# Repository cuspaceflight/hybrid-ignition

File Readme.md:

# Hybrid Rocket Engine Ignition System

This repository contains the design files for the valve controller used by CU Spaceflight to control our hybrid rocket engine. It is capable of actuating up to 10x 24W solenoid valves simultaneously and is controlled over RS422 or USB by a GUI. 

### Repository Layout

* **ChibiOS:** ChibiOS RTOS, developed by Giovanni Di Sirio.
* **agg-kicad:** KiCAD libraries, footprints and scripts developed by Adam Greig.
* **gen-board.h:** Python tool for generating 'board.h' header files for STM32 microcontrollers for use with ChibiOS.
* **m4-gcs:** Python GUI used to control and monitor the valve controller, developed by Greg Brooks.
* **pcb:** Hardware design files including schematic, pcb layout and BOM.
    * **comms:** Communications board project files.
    * **ignition:** Ignition board project files.
    * **lib:** Various schematic symbols.
* **firmware:** Firmware for each of the three sub-systems.
    * **comms-relay:** Full duplex USB to RS422 converter.
    * **comms-router:** Communications interface for the valve controller. Handles receiving packets over RS422 and routing to the firing boards over UART and vice-versa.
    * **ignition:** Actuates valves on command and reports measurements such as currents consumption, output voltage and if the valve coil is plugged in or not.

Developed by Matt Coates (mc955).

### Future Modifications
* The firing LEDs have their cathodes driven to 24v when a channel is armed but not firing. These LEDs should be moved to be driven by the GPIO that drives the gate of the firing FET.
* Flyback diodes are required on the output channels.

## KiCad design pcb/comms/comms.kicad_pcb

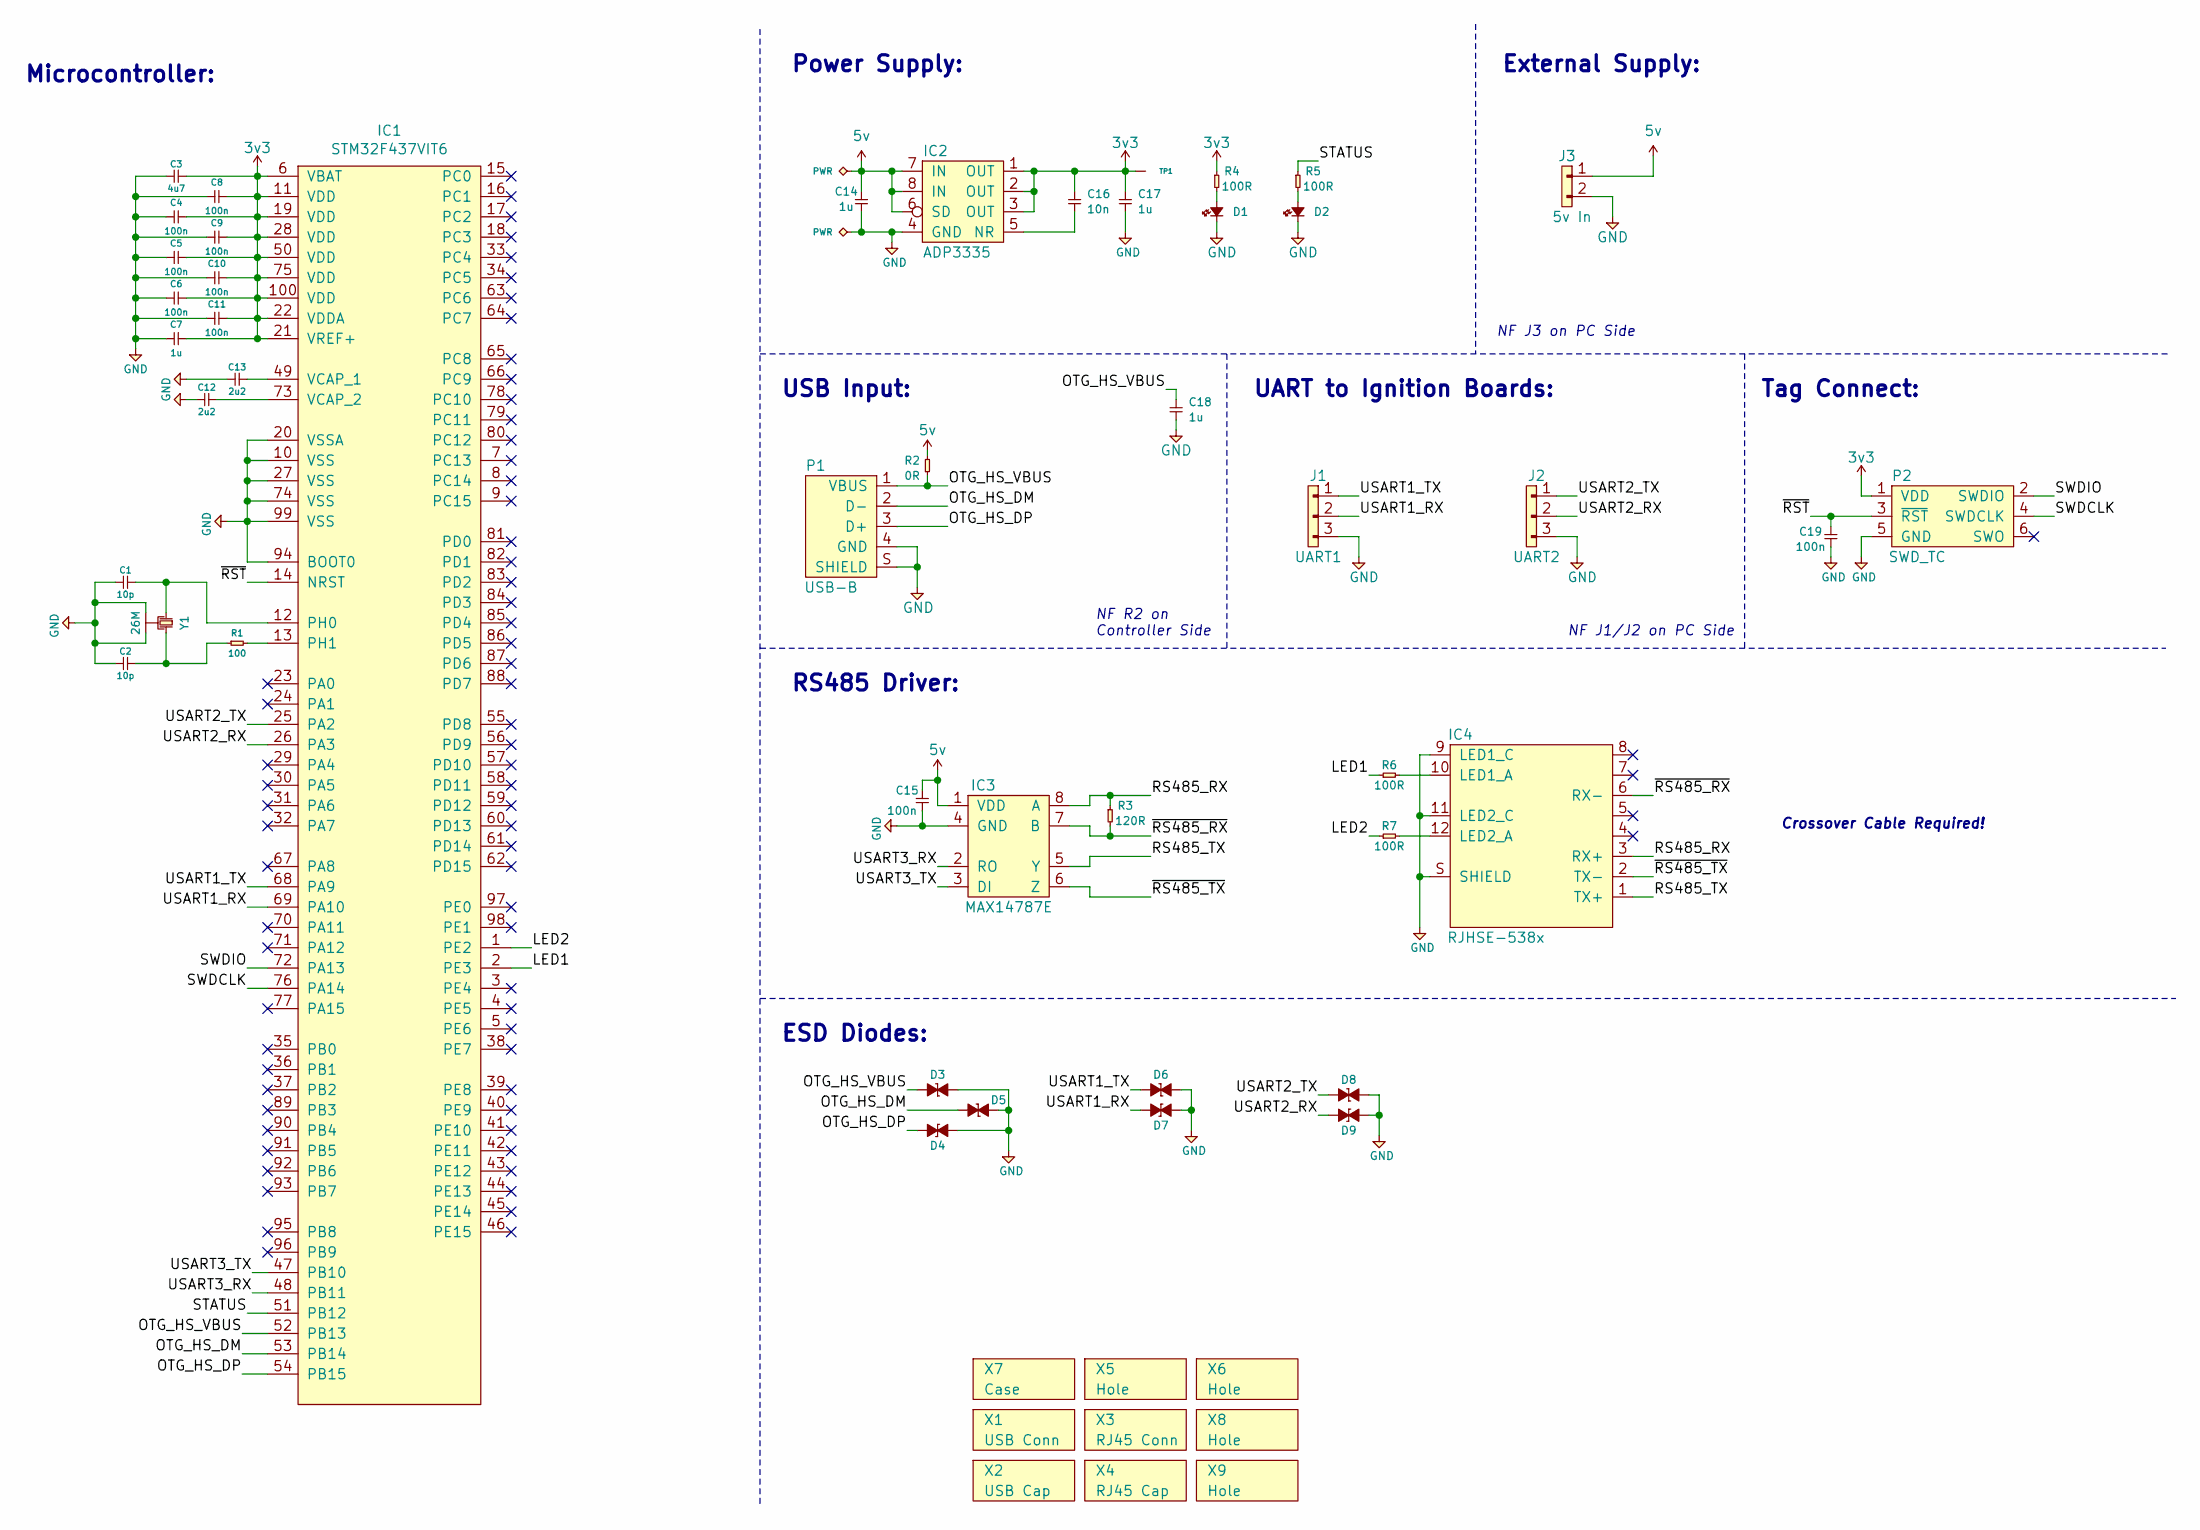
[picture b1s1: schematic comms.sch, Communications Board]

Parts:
C1, C2: 10p; 0402; Farnell 2496790
C3: 4u7; 0402; Farnell 2426952
C4, C5, C6, C8, C9, C10, C11, C15, C19: 100n; 0402; Farnell 2496771
C7: 1u; 0402; Farnell 2496814
C12, C13: 2u2; 0402; Farnell 2362088
C14, C17, C18: 1u; 0603-L; Farnell 1865556
C16: 10n; 0603-L; Farnell 2496825
D1, D2: LED; 0603-LED; Farnell 2290328
D3, D4, D5, D6, D7, D8, D9: ESD_DIODE; 0402; Farnell 2368169
IC1: STM32F437VIT6; LQFP-100; Farnell 2333377
IC2: ADP3335; MSOP-8; Farnell 2067775
IC3: MAX14787E; SOIC-8; Farnell 2528531
IC4: RJHSE-538x; RJHSE-538X; Farnell 1462758
J1: UART1; S03B-PASK-2; Farnell 1830748
J2: UART2; S03B-PASK-2; Farnell 1830748
J3: 5v In; S02B-PASK-2; Farnell 1830747
P1: USB-B; USB-B-SKT; Farnell 1753809
P2: SWD_TC; TC2030-NL
R1: 100; 0402; Farnell 9239111
R2: 0R; 0603; Farnell 2122112
R3: 120R; 0402; Farnell 2140682
R4, R5, R6, R7: 100R; 0603; Farnell 2616742
TP1: TESTPAD
X1: USB Conn
X2: USB Cap
X3: RJ45 Conn
X4: RJ45 Cap
X5, X6, X8, X9: Hole; M3_MOUNT
X7: Case; Farnell 9287787
Y1: 26M; XTAL-20x16; Farnell 2506952

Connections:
3v3: C3.2, C4.2, C5.2, C6.2, C7.2, C8.2, C9.2, C10.2, C11.2, C16.1, C17.1, IC1.6 (VBAT), IC1.11 (VDD), IC1.19 (VDD), IC1.21 (VREF+), IC1.22 (VDDA), IC1.28 (VDD), IC1.50 (VDD), IC1.75 (VDD), IC1.100 (VDD), IC2.1 (OUT), IC2.2 (OUT), IC2.3 (OUT), P2.1 (VDD), R4.1, TP1.1
5v: C14.1, C15.2, IC2.6 (SD), IC2.7 (IN), IC2.8 (IN), IC3.1 (VDD), J3.1, R2.2
/LED1: IC1.2 (PE3), R6.1
/LED2: IC1.1 (PE2), R7.1
/OTG_HS_DM: D5.1, IC1.53 (PB14), P1.2 (D-)
/OTG_HS_DP: D4.1, IC1.54 (PB15), P1.3 (D+)
/OTG_HS_VBUS: C18.1, D3.1, IC1.52 (PB13), P1.1 (VBUS), R2.1
/RS485_RX: IC3.8 (A), IC4.3 (RX+), R3.1
/RS485_TX: IC3.5 (Y), IC4.1 (TX+)
/STATUS: IC1.51 (PB12), R5.1
/SWDCLK: IC1.76 (PA14), P2.4 (SWDCLK)
/SWDIO: IC1.72 (PA13), P2.2 (SWDIO)
/USART1_RX: D7.1, IC1.69 (PA10), J1.2
/USART1_TX: D6.1, IC1.68 (PA9), J1.1
/USART2_RX: D9.1, IC1.26 (PA3), J2.2
/USART2_TX: D8.1, IC1.25 (PA2), J2.1
/USART3_RX: IC1.48 (PB11), IC3.2 (RO)
/USART3_TX: IC1.47 (PB10), IC3.3 (DI)
/~RS485_RX: IC3.7 (B), IC4.6 (RX-), R3.2
/~RS485_TX: IC3.6 (Z), IC4.2 (TX-)
/~RST: C19.2, IC1.14 (NRST), P2.3 (~RST)
GND: C1.1, C2.1, C3.1, C4.1, C5.1, C6.1, C7.1, C8.1, C9.1, C10.1, C11.1, C12.2, C13.2, C14.2, C15.1, C17.2, C18.2, C19.1, D1.1, D2.1, D3.2, D4.2, D5.2, D6.2, D7.2, D8.2, D9.2, IC1.10 (VSS), IC1.20 (VSSA), IC1.27 (VSS), IC1.74 (VSS), IC1.94 (BOOT0), IC1.99 (VSS), IC2.4 (GND), IC3.4 (GND), IC4.9 (LED1_C), IC4.11 (LED2_C), IC4.S (SHIELD), J1.3, J2.3, J3.2, P1.4 (GND), P1.S (SHIELD), P2.5 (GND), Y1.2, Y1.4
unnamed: C1.2, IC1.12 (PH0), Y1.1
unnamed: C2.2, R1.1, Y1.3
unnamed: C12.1, IC1.73 (VCAP_2)
unnamed: C13.1, IC1.49 (VCAP_1)
unnamed: C16.2, IC2.5 (NR)
unnamed: D1.2, R4.2
unnamed: D2.2, R5.2
unnamed: IC1.13 (PH1), R1.2
unnamed: IC4.10 (LED1_A), R6.2
unnamed: IC4.12 (LED2_A), R7.2

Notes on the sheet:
Microcontroller:
Power Supply:
Tag Connect:
USB Input:
External Supply:
RS485 Driver:
UART to Ignition Boards:
Crossover Cable Required!
NF J1/J2 on PC Side
NF J3 on PC Side
NF R2 on Controller Side
ESD Diodes:

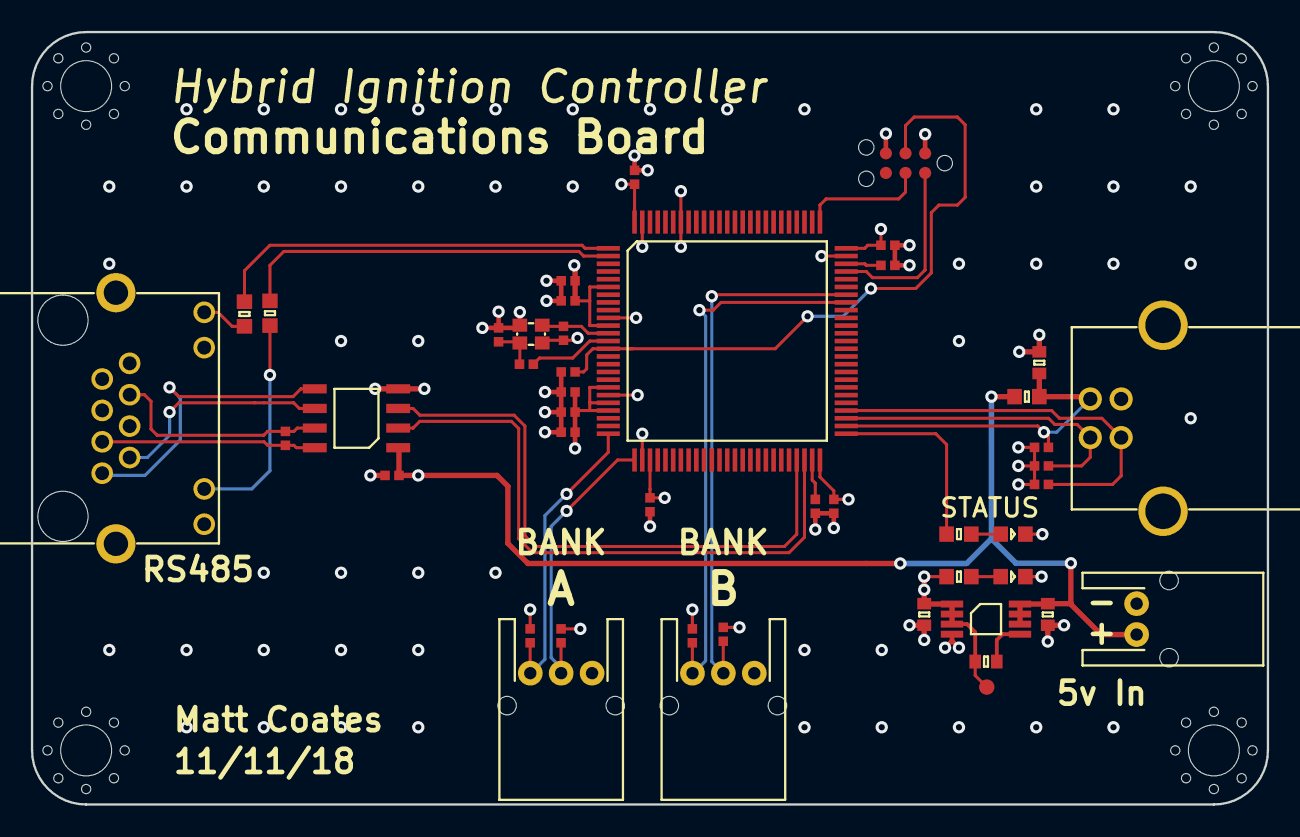
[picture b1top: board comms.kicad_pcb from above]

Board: 4 copper layers, 80.0 x 50.0 mm, 50 parts (0 on the bottom side), 32 nets.

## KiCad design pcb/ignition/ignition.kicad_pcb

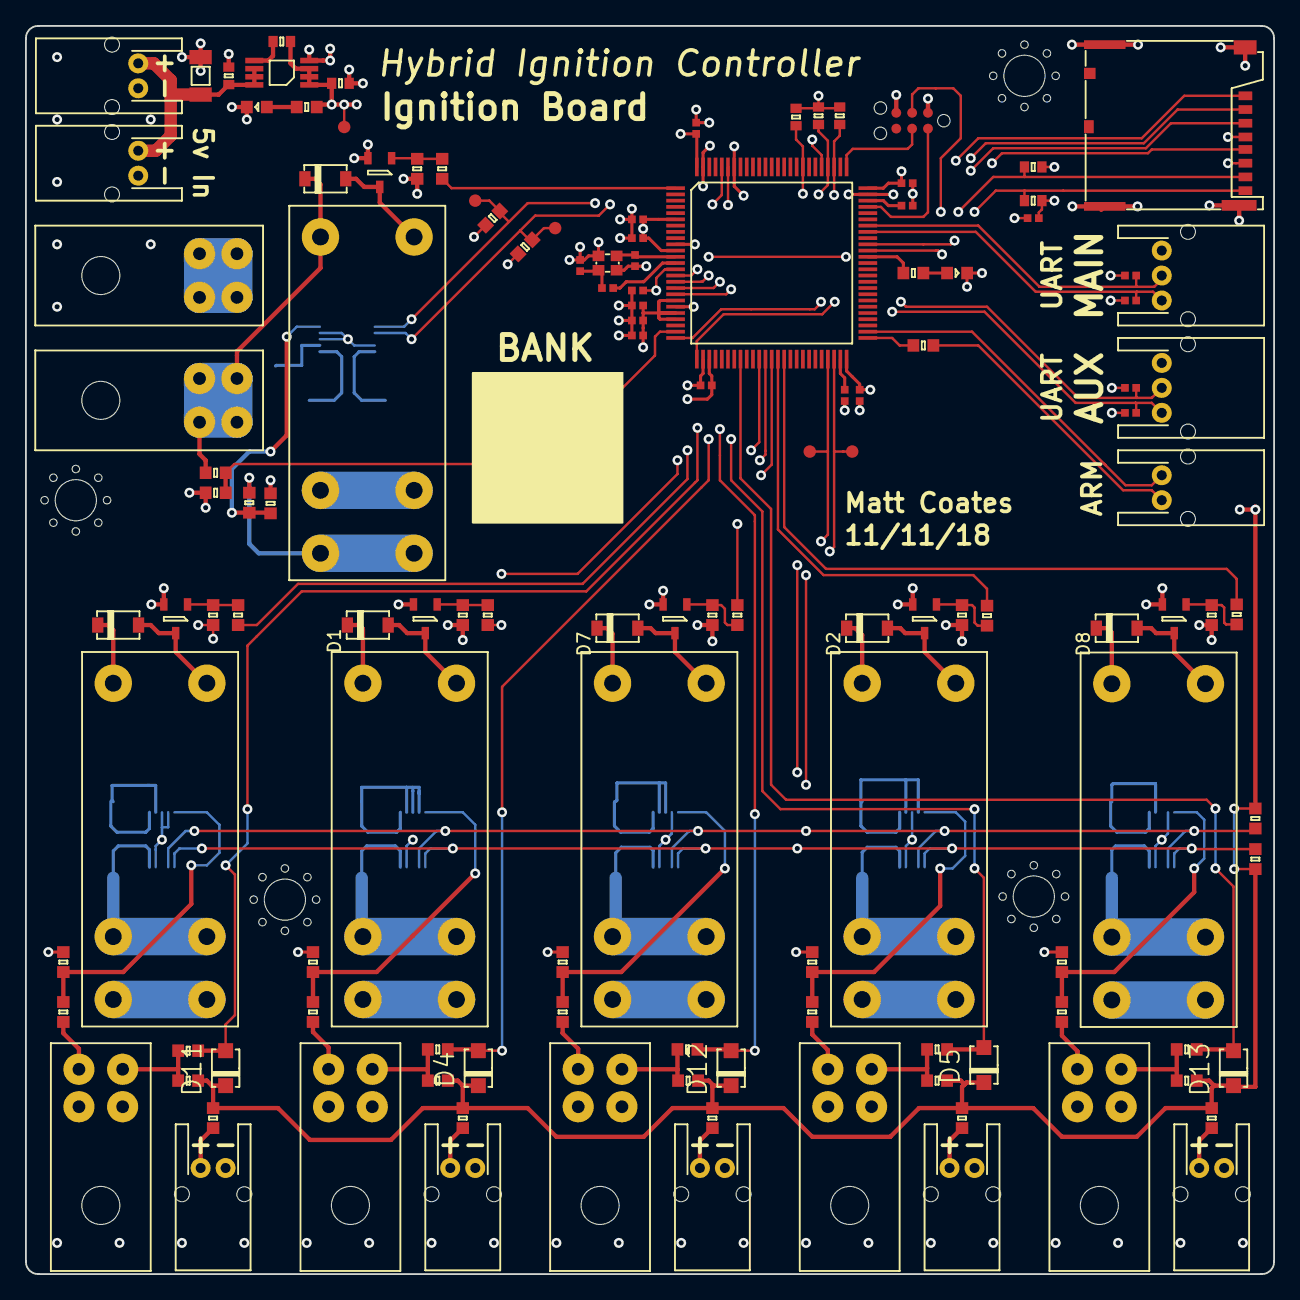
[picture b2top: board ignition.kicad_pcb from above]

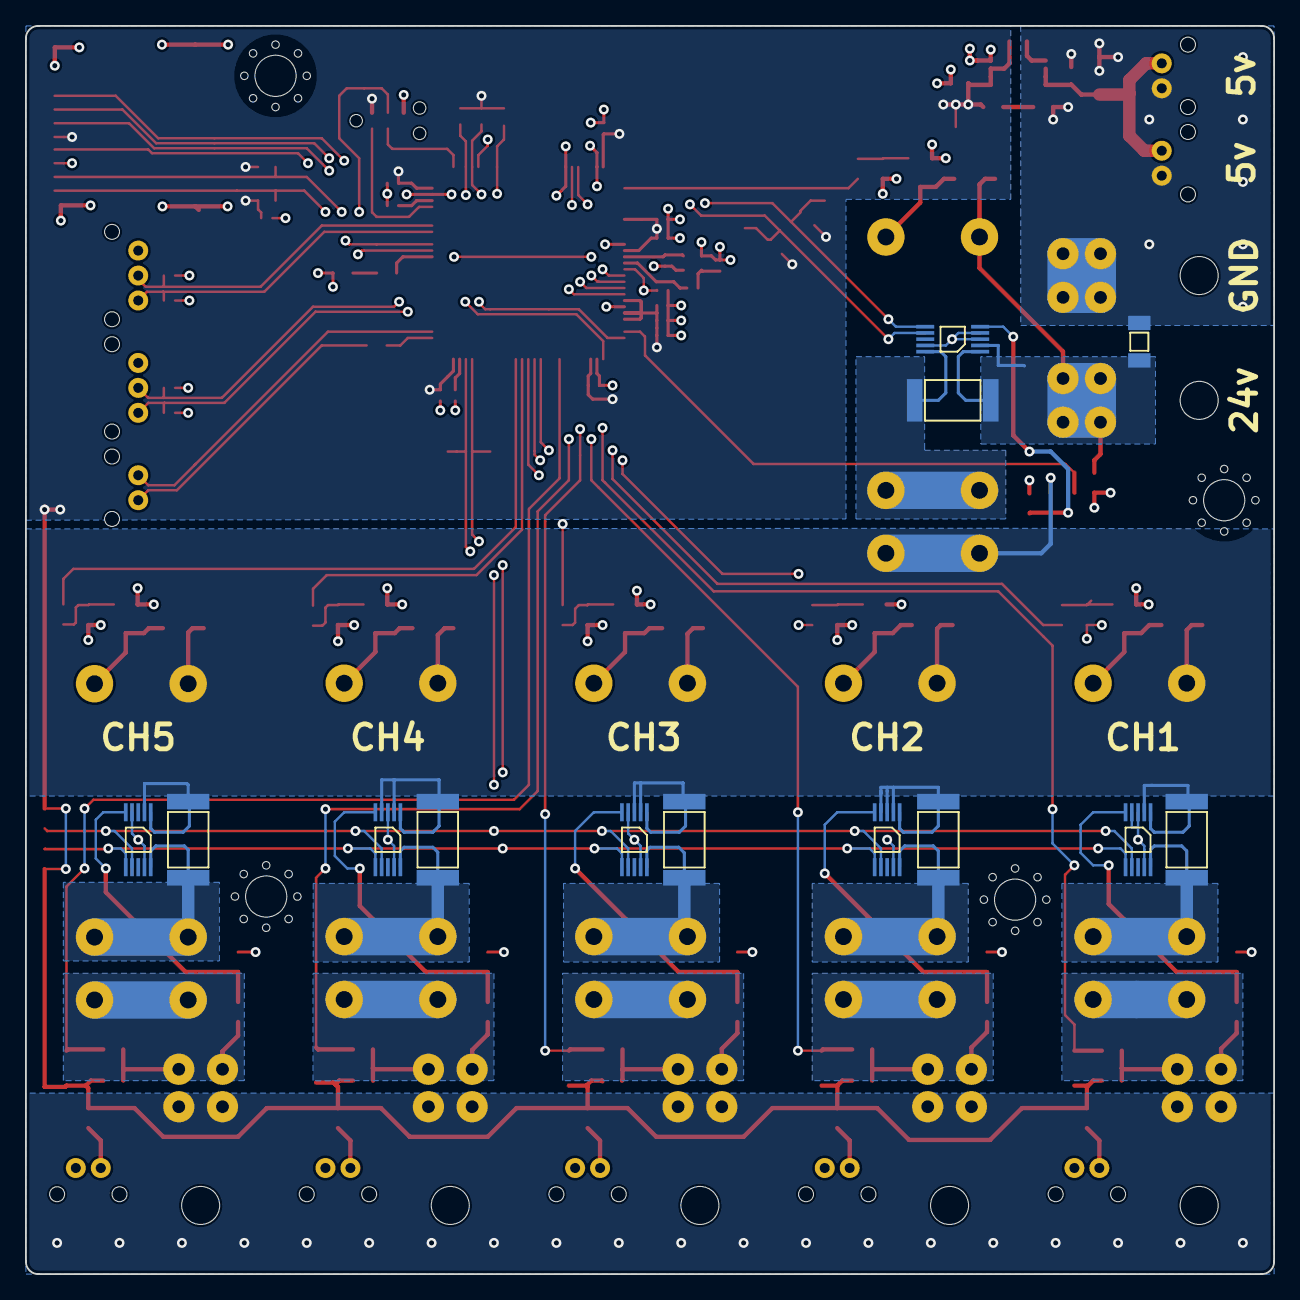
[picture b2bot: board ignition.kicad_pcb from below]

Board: 4 copper layers, 100.0 x 100.0 mm, 146 parts (13 on the bottom side), 80 nets.

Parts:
C1, C2: 10u; 1206
C3, C5: 1u; 0603-L
C4: 10n; 0603-L
C6, C7: 10p; 0402
C8: 4u7; 0402
C9, C10, C11, C13, C14, C15, C16, C19, C20: 100n; 0402
C12: 1u; 0402
C17, C18: 2u2; 0402
D1, D2, D3, D6, D7, D8: SCHOTTKY; SOD-123FL
D4, D5, D11, D12, D13: D; SOD-123F
D9, D10: LED; 0603-LED
D14, D15, D16, D17: ESD_DIODE; 0402
IC1, IC2, IC3, IC4, IC5, IC6: LTC4151; MSOP-10
IC7: ADP3335; MSOP-8
IC8: STM32F437VIT6; LQFP-100
J1, J3: PSU; 172316-1104
J2: LED1; S02B-PASK-2
J4: LED2; S02B-PASK-2
J5: 5v In; S02B-PASK-2
J6: 5v Out; S02B-PASK-2
J7: LED3; S02B-PASK-2
J8: LED4; S02B-PASK-2
J9: LED5; S02B-PASK-2
J10: CH2; 172316-1104
J11: CH4; 172316-1104
J12: ARM; S02B-PASK-2
J13: UART1; S03B-PASK-2
J14: UART2; S03B-PASK-2
J15: CH1; 172316-1104
J16: CH3; 172316-1104
J17: CH5; 172316-1104
K1, K2, K3, K4, K5, K6: 16A SPST; RT33L024
P1: SWD_TC; TC2030-NL
Q1, Q2, Q3, Q4, Q5, Q6: NFET; SOT-23
R1, R4, R12, R17, R24: 56R; 0603
R2, R5, R6, R11, R25, R26, R28, R29, R30, R52, R53, R54: 10k; 0603
R3, R9, R10, R14, R15, R16, R20, R34, R35, R36, R38, R39, R40: 110k; 0603
R7, R8, R31, R32, R33: 0.05R; 2512
R13: 0.01R; 2512
R18, R19, R21, R27, R37, R42, R43, R44, R46: 100R; 0603
R22, R23, R41, R45, R47, R48, R49, R50, R51: 1k; 0603
R55, R56, R57, R58, R59: 47k; 0603-L
R60: 100; 0402
TP1, TP2, TP3, TP4, TP5: TESTPAD
U1: MICROSD; MICROSD_MOLEX_503398-1892
X33, X34, X35, X36: Hole; M3_MOUNT
Y1: 26M; XTAL-20x16

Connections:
3v3: C4.1, C5.1, C8.2, C9.2, C10.2, C11.2, C12.2, C13.2, C14.2, C15.2, C16.2, C19.1, D4.1, D5.1, D11.1, D12.1, D13.1, IC7.1, IC7.2, IC7.3, IC8.6, IC8.11, IC8.19, IC8.21, IC8.22, IC8.28, IC8.50, IC8.75, IC8.100, P1.1, R1.2, R4.2, R12.2, R17.2, R22.2, R23.2, R24.2, R37.1, R41.2, R45.2, R47.2, R48.2, R49.2, R50.2, R51.2, R55.1, R56.1, R57.1, R58.1, R59.1, TP1.1, U1.4
5v: C2.1, C3.1, IC7.6, IC7.7, IC7.8, J5.1, J6.1
/ARM_GRN: IC8.51, R27.2
/ARM_RED: IC8.52, J12.2
/ARM_SUPPLY: IC8.1, R21.1
/CH1: J15.1, J15.2, K4.4, R34.1, R49.1, R52.1
/CH1_CONT: D11.2, IC8.15, R52.2
/CH1_FIRE: IC8.36, R42.1
/CH2: J10.1, J10.2, K1.4, R9.1, R22.1, R25.1
/CH2_CONT: D4.2, IC8.16, R25.2
/CH2_FIRE: IC8.37, R18.1
/CH3: J16.1, J16.2, K5.4, R35.1, R50.1, R53.1
/CH3_CONT: D12.2, IC8.17, R53.2
/CH3_FIRE: IC8.38, R43.1
/CH4: J11.1, J11.2, K2.4, R10.1, R23.1, R26.1
/CH4_CONT: D5.2, IC8.18, R26.2
/CH4_FIRE: IC8.39, R19.1
/CH5: J17.1, J17.2, K6.4, R36.1, R51.1, R54.1
/CH5_CONT: D13.2, IC8.33, R54.2
/CH5_FIRE: IC8.40, R44.1
/FIRE_DIST: D1.1, D2.1, D6.1, D7.1, D8.1, IC1.1, IC1.2, IC1.3, IC1.4, IC2.1, IC2.2, IC2.4, IC4.1, IC4.2, IC5.1, IC5.2, IC5.3, IC6.1, IC6.2, K1.2, K2.2, K3.4, K4.2, K5.2, K6.2, R7.2, R8.2, R14.1, R31.2, R32.2, R33.2
/I2C1_SCL: IC3.6, IC8.95, R47.1, TP4.1
/I2C1_SDA: IC3.7, IC8.96, R48.1, TP5.1
/I2C2_SCL: IC1.6, IC2.6, IC4.6, IC5.6, IC6.6, IC8.47, R41.1, TP2.1
/I2C2_SDA: IC1.7, IC2.7, IC4.7, IC5.7, IC6.7, IC8.48, R45.1, TP3.1
/LED1: D6.2, J2.2, K4.1, Q4.3
/LED2: D1.2, J4.2, K1.1, Q1.3
/LED3: D7.2, J7.2, K5.1, Q5.3
/LED4: D2.2, J8.2, K2.1, Q2.3
/LED5: D8.2, J9.2, K6.1, Q6.3
/PSU_MON: IC8.24, R2.1, R3.1
/SDIO_CK: IC8.80, U1.5
/SDIO_CMD: IC8.83, R59.2, U1.3
/SDIO_D0: IC8.65, R55.2, U1.7
/SDIO_D1: IC8.66, R56.2, U1.8
/SDIO_D2: IC8.78, R57.2, U1.1
/SDIO_D3: IC8.79, R58.2, U1.2
/STATUS: IC8.64, R46.1
/SWDCLK: IC8.76, P1.4
/SWDIO: IC8.72, P1.2
/USART1_RX: D15.1, IC8.69, J13.2
/USART1_TX: D14.1, IC8.68, J13.1
/USART2_RX: D17.1, IC8.26, J14.2
/USART2_TX: D16.1, IC8.25, J14.1
/~RST: C20.2, IC8.14, P1.3
GND: C1.2, C2.2, C3.2, C5.2, C6.1, C7.1, C8.1, C9.1, C10.1, C11.1, C12.1, C13.1, C14.1, C15.1, C16.1, C17.2, C18.2, C19.2, C20.1, D9.1, D10.1, D14.2, D15.2, D16.2, D17.2, IC1.9, IC2.3, IC2.9, IC3.3, IC3.4, IC3.9, IC4.3, IC4.4, IC4.9, IC5.4, IC5.9, IC6.4, IC6.9, IC7.4, IC8.10, IC8.20, IC8.27, IC8.74, IC8.94, IC8.99, J3.1, J3.2, J3.3, J3.4, J5.2, J6.2, J10.3, J10.4, J11.3, J11.4, J13.3, J14.3, J15.3, J15.4, J16.3, J16.4, J17.3, J17.4, P1.5, Q1.2, Q2.2, Q3.2, Q4.2, Q5.2, Q6.2, R2.2, R5.1, R6.1, R11.1, R15.1, R16.1, R20.1, R28.1, R29.1, R30.1, R38.1, R39.1, R40.1, U1.6, U1.9, Y1.2, Y1.4
unnamed: C4.2, IC7.5
unnamed: C6.2, IC8.12, Y1.1
unnamed: C7.2, R60.1, Y1.3
unnamed: C17.1, IC8.73
unnamed: C18.1, IC8.49
unnamed: D3.2, K3.1, Q3.3
unnamed: D9.2, R37.2
unnamed: D10.2, R46.2
unnamed: IC1.5, R5.2, R9.2
unnamed: IC1.10, K1.3, R7.1
unnamed: IC2.5, R6.2, R10.2
unnamed: IC2.10, K2.3, R8.1
unnamed: IC3.5, R11.2, R14.2
unnamed: IC3.10, K3.3, R13.1
unnamed: IC4.5, R28.2, R34.2
unnamed: IC4.10, K4.3, R31.1
unnamed: IC5.5, R29.2, R35.2
unnamed: IC5.10, K5.3, R32.1
unnamed: IC6.5, R30.2, R36.2
unnamed: IC6.10, K6.3, R33.1
unnamed: IC8.13, R60.2
unnamed: J2.1, R1.1
unnamed: J4.1, R4.1
unnamed: J7.1, R12.1
unnamed: J8.1, R17.1
unnamed: J9.1, R24.1
unnamed: J12.1, R27.1
unnamed: Q1.1, R15.2, R18.2
unnamed: Q2.1, R16.2, R19.2
unnamed: Q3.1, R20.2, R21.2
unnamed: Q4.1, R38.2, R42.2
unnamed: Q5.1, R39.2, R43.2
unnamed: Q6.1, R40.2, R44.2
VCC: C1.1, D3.1, IC3.1, IC3.2, J1.1, J1.2, J1.3, J1.4, K3.2, R3.2, R13.2

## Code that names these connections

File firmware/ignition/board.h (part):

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 *  GPIOA setup:
 *
 * PA0  - PIN0                         (unused).
 * PA1  - PSU_MON                      (analog floating).
 * PA2  - PIN2                         (unused).
 * PA3  - PIN3                         (unused).
 * PA4  - PIN4                         (unused).
 * PA5  - PIN5                         (unused).
 * PA6  - PIN6                         (unused).
 * PA7  - PIN7                         (unused).
 * PA8  - PIN8                         (unused).
 * PA9  - UART_MAIN_TX                 (af7).
 * PA10 - UART_MAIN_RX                 (af7).
 * PA11 - PIN11                        (unused).
 * PA12 - PIN12                        (unused).
 * PA13 - SWDIO                        (af0).
 * PA14 - SWCLK                        (pulldown af0).
 * PA15 - PIN15                        (unused).
*/
#define VAL_GPIOA_MODER                (PIN_MODE_INPUT(GPIOA_PIN0) | \
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 *  GPIOB setup:
 *
 * PB0  - PIN0                         (unused).
 * PB1  - CH1_FIRE                     (output pushpull startlow pulldown).
 * PB2  - CH2_FIRE                     (output pushpull startlow pulldown).
 * PB3  - PIN3                         (unused).
 * PB4  - PIN4                         (unused).
 * PB5  - PIN5                         (unused).
 * PB6  - PIN6                         (unused).
 * PB7  - PIN7                         (unused).
 * PB8  - I2C1_SCL                     (af4 opendrain).
 * PB9  - I2C1_SDA                     (af4 opendrain).
 * PB10 - I2C2_SCL                     (af4 opendrain).
 * PB11 - I2C2_SDA                     (af4 opendrain).
 * PB12 - ARM_GRN                      (output pushpull startlow).
 * PB13 - ARM_RED                      (output pushpull startlow).
 * PB14 - PIN14                        (unused).
 * PB15 - PIN15                        (unused).
*/
#define VAL_GPIOB_MODER                (PIN_MODE_INPUT(GPIOB_PIN0) | \
                                        PIN_MODE_OUTPUT(GPIOB_CH1_FIRE) | \
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/*
 *  GPIOC setup:
 *
 * PC0  - CH1_CONT                     (analog floating).
 * PC1  - CH2_CONT                     (analog floating).
 * PC2  - CH3_CONT                     (analog floating).
 * PC3  - CH4_CONT                     (analog floating).
 * PC4  - CH5_CONT                     (analog floating).
 * PC5  - PIN5                         (unused).
 * PC6  - PIN6                         (unused).
 * PC7  - STATUS                       (output pushpull startlow).
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 *
 * PE0  - PIN0                         (unused).
 * PE1  - PIN1                         (unused).
 * PE2  - ARM_SUPPLY                   (output pushpull startlow pulldown).
 * PE3  - PIN3                         (unused).
 * PE4  - PIN4                         (unused).
 * PE5  - PIN5                         (unused).
 * PE6  - PIN6                         (unused).
 * PE7  - CH3_FIRE                     (output pushpull startlow pulldown).
 * PE8  - CH4_FIRE                     (output pushpull startlow pulldown).
 * PE9  - CH5_FIRE                     (output pushpull startlow pulldown).
 * PE10 - PIN10                        (unused).
 * PE11 - PIN11                        (unused).
 * PE12 - PIN12                        (unused).
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/*
 *  GPIOH setup:
 *
 * PH0  - PIN0                         (unused).
 * PH1  - PIN1                         (unused).
 * PH2  - PIN2                         (unused).
 * PH3  - PIN3                         (unused).
 * PH4  - PIN4                         (unused).
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
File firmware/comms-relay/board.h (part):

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 *
 * PA0  - PIN0                         (unused).
 * PA1  - PIN1                         (unused).
 * PA2  - PIN2                         (unused).
 * PA3  - PIN3                         (unused).
 * PA4  - PIN4                         (unused).
 * PA5  - PIN5                         (unused).
 * PA6  - PIN6                         (unused).
 * PA7  - PIN7                         (unused).
 * PA8  - PIN8                         (unused).
 * PA9  - PIN9                         (unused).
 * PA10 - PIN10                        (unused).
 * PA11 - PIN11                        (unused).
 * PA12 - PIN12                        (unused).
 * PA13 - SWDIO                        (af0).
 * PA14 - SWCLK                        (pulldown af0).
 * PA15 - PIN15                        (unused).
*/
#define VAL_GPIOA_MODER                (PIN_MODE_INPUT(GPIOA_PIN0) | \
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 * PB7  - PIN7                         (unused).
 * PB8  - PIN8                         (unused).
 * PB9  - PIN9                         (unused).
 * PB10 - RS485_TX                     (af7).
 * PB11 - RS485_RX                     (af7).
 * PB12 - STATUS                       (output pushpull startlow).
 * PB13 - OTG_VBUS                     (input pulldown).
 * PB14 - OTG_HS_DM                    (af12).
 * PB15 - OTG_HS_DP                    (af12).
*/
#define VAL_GPIOB_MODER                (PIN_MODE_INPUT(GPIOB_PIN0) | \
                                        PIN_MODE_INPUT(GPIOB_PIN1) | \
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 *
 * PE0  - PIN0                         (unused).
 * PE1  - PIN1                         (unused).
 * PE2  - LED2                         (output pushpull startlow).
 * PE3  - LED1                         (output pushpull startlow).
 * PE4  - PIN4                         (unused).
 * PE5  - PIN5                         (unused).
 * PE6  - PIN6                         (unused).
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/*
 *  GPIOH setup:
 *
 * PH0  - PIN0                         (unused).
 * PH1  - PIN1                         (unused).
 * PH2  - PIN2                         (unused).
 * PH3  - PIN3                         (unused).
 * PH4  - PIN4                         (unused).
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
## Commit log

2018-10-22 started project
2018-10-22 started psu
2018-10-22 Use relativr path in .gitmodules
2018-10-24 arming circuit done, started ch1 but need to add continuity
2018-10-29 added valve channels
2018-11-02 made progress
2018-11-03 finished schematic
2018-11-03 changed key switch
2018-11-03 finalised schematic, started pcb component placement
2018-11-06 ignition pcb almost complete
2018-11-07 pcb routing finished
2018-11-09 finished comms schematic
2018-11-11 finished comms board
2018-11-11 finalised schematic and pcb copper, adding silk
2018-11-11 pcbs complete
2018-11-11 made changes to ignition as per review
2018-11-11 made changes to comms as per review
2018-11-12 generated gerbers for comms
2018-11-12 generated gerbers for ignition
2018-11-12 production ready gerbers for ignition
2018-11-12 production ready gerbers
2018-11-25 added Boms
2018-11-26 added readme
2018-12-21 generated final sticker bom
2018-12-21 defined packets
2018-12-21 Imported ChibiOS
2018-12-21 comms-relay firmware template
2018-12-21 successfully sent and recieved some bytes
2018-12-24 usb serial and packet router finished, ready to test usb loopback
2018-12-24 succesful test
2018-12-24 fixed overflow issue and tested router speed
2018-12-24 changed rx timeout
2018-12-24 fw ready to test
2018-12-27 changed comment in rs422.c and added ignition board.yaml
2018-12-28 testing i2c
2018-12-28 ltc4151 template half done
2018-12-29 tested working analog driver
2018-12-31 working ltc4151 driver
2019-01-02 successful test of ADC and LTC4151s
2019-01-02 updated packet def
2019-01-03 packet routing comms board almost finished
2019-01-03 comms relay and router finished and tested
2019-01-03 added config packet
2019-01-05 added broadcast func to router
2019-01-05 changed packets.h and made progress on ignition fw
2019-01-06 changed checksum method to mod 65535
2019-01-06 init and isolation states working
2019-01-06 state machine progress, arm command works
2019-01-06 safe state working, now just to finish arm
2019-01-06 added checksum condition on destination check
2019-01-06 state machine done
2019-01-16 import pc side software

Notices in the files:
firmware/comms-relay/board.h:
ChibiOS - Copyright (C) 2006..2016 Giovanni Di Sirio
Licensed under the Apache License, Version 2.0 (the "License");
